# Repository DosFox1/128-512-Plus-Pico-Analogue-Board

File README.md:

**A Pico ATX and Pi Pico Power Supply and Scan Converter for the Macintosh 128/512/Plus**

A board to power a Macintosh 128/512/Plus from a Pico ATX PSU, as well as to generate a VGA video signal from an onboard Pico scan converter.
This board was designed inconjunction with the Sony SND Replacement to support my work on the Macintosh Plus clone.

**So, What Is It?**

This is a combined power supply and VGA scan converter for a Macintosh 128/512 or Plus.
The VGA scan converter is based off the work by the GuruThree:
https://github.com/guruthree/mac-se-video-converter

The firmware for the Pico is available within that repository.
The hardware for the VGA scan converter is based off of the VGA reference design as provided here:
https://datasheets.raspberrypi.com/rp2040/hardware-design-with-rp2040.pdf

The PSU portion of the deisgn is intended to be used with a Pico PSU, although any suitable ATX PSU can be used. 
The connector is identical to that of the Macintosh 128/512/Plus, so either a Molex KK396 11 way connector can be installed with an appropriate cable,
or the board can be soldered directly to the Macintosh Logic Board.
 
VDEV1 units have been assembled and worked first time. No modifications to the board were necessary at all. Additionally, I have built an equivalent system using a Pimoroni VGA board (as per the original repository) and with a Pico ATX PSU.

**Additional Features**

Aside from providing Power and a VGA signal from the Logic board, it also has some additional features:

1) Option for Composite Video with associated jumper -  the scan converter can be compiled to generate a PAL video signal from the red channel,
as such, there is an RCA connector with a jumper to select whether the required output.
Please note that the firmware will need to be recompiled with the PAL video option, and the video signal is known to be quite poor.
It's something to be fixed at some point.

2) Pads for -5v and -12V, as well as a -5v regulator - the regulator and pads are provided in case the user is intending to use the Sony SND replacement
(https://github.com/DosFox1/Sony-SND-THT-Replacement/tree/main), or if a board is installed that requires off board -5v to be regulated (such as an SE)
In normal operation, the -5v regulator and pads are not needed, and can be DNF'd (Do Not Fit).

3) Optional potential divider - the original scan converter does call for the use of a standard voltage level shifter, it was found that the 128/512/Plus appear to output
a signal that was lower than what the level shifter expected, resulting in the system not working. Further investigation reveals that the output from the board is in the region
of 3.8v - which is in the limits of a V1 Pico, as well as V2 Pico (which are 5v tolerant). Regardless, current limiting resistors have been added, and if so desired, additional resistors can be added (or diodes!) for added protection. This is a VDEV1 design, so extra protection may be added for the next iteration. Your mileage may vary!

5) Speaker pin header - the speaker output is routed to a separate pin header, to make it easier to add an external speaker.

6) RTC diodes and battery option - two diodes have been added, as well as an additional header to add a 4.5v battery pack for the RTC.
I would suggest ensuring that the battery pack is stored well away from the logic board and the analogue board, to avoid battery leakage.

7) Power Supply Switch with pads - external power switch with pads has been added, allowing the user to install either a switch at the rear of the unit, or to add an external toggle switch to power the system on, if so desired.

8) Onboard Power LED and external pads - onboard power LED is provided to prove that the 5v rail has powered up. Also the option to mount an LED elsewhere within the case if so desired.

**Part List**

Much like the Sony SND, the parts are relatively easy to source, although there may be some difficulty finding the precision value resistors. 
The parts are as follows:

<pre>
Part     Value            Device                       Package                 Library             Sheet

C1       100n 50V         100N_TH_CAP                  CAP_5.08MM_PITCH        Capacitors TH       1
C2       100n 50V         100N_TH_CAP                  CAP_5.08MM_PITCH        Capacitors TH       1
CN1      V06-1x20-SV-GF-1 PICO_BOARD                   PICO_SOCKET             uProcessor          1
CN2      2way             PIN_HEADER_2W_VERT_TH        2W_2.54MM_PITCH_VERT_TH Connectors          1
CN3      2way             PIN_HEADER_2W_VERT_TH        2W_2.54MM_PITCH_VERT_TH Connectors          1
CN4      V06-1x3-SV-GF-1  PIN_HEADER_3W_VERT_FEMALE_TH 3W_2.54MM_PITCH_VERT_TH Connectors          1
CN5      2way             PIN_HEADER_2W_VERT_TH        2W_2.54MM_PITCH_VERT_TH Connectors          1
CN6      2way             PIN_HEADER_2W_VERT_TH        2W_2.54MM_PITCH_VERT_TH Connectors          1
CN7      DB15             DB15                         DB15                    SparkFun-Retired    1
CN8      ATX24RH          ATX24RH                      ATX24_RIGHT_ANGLE       SparkFun-Connectors 1
CN9      RCA              RCA                          RCA                     SparkFun-Connectors 1
CN10     11 Way KK        KK-156-11                    KK-156-11               con-molex           1
D1       1N4004           1N4004                       DO41-10                 adafruit            1
D2       1N4004           1N4004                       DO41-10                 adafruit            1
LED1     Red              5MM_LED_RED                  5MM_TH_VERT_STANDARD    Optoelectronics     1
R1       470R             470R_TH_RESISTOR             RESISTORTHRUHOLE        Resistors TH        1
R2       47R              47R_TH_RESISTOR              RESISTORTHRUHOLE        Resistors TH        1
R3       47R              47R_TH_RESISTOR              RESISTORTHRUHOLE        Resistors TH        1
R4       1k               1K_TH_RESISTOR               RESISTORTHRUHOLE        Resistors TH        1
R5       2k               2K_TH_RESISTOR               RESISTORTHRUHOLE        Resistors TH        1
R6       4k02             4K02_TH_RESISTOR             RESISTORTHRUHOLE        Resistors TH        1
R7       8k06             8K06_TH_RESISTOR             RESISTORTHRUHOLE        Resistors TH        1
R8       499R             499R_TH_RESISTOR             RESISTORTHRUHOLE        Resistors TH        1
R9       1k               1K_TH_RESISTOR               RESISTORTHRUHOLE        Resistors TH        1
R10      2k               2K_TH_RESISTOR               RESISTORTHRUHOLE        Resistors TH        1
R11      4k02             4K02_TH_RESISTOR             RESISTORTHRUHOLE        Resistors TH        1
R12      8k06             8K06_TH_RESISTOR             RESISTORTHRUHOLE        Resistors TH        1
R13      499R             499R_TH_RESISTOR             RESISTORTHRUHOLE        Resistors TH        1
R14      1k               1K_TH_RESISTOR               RESISTORTHRUHOLE        Resistors TH        1
R15      2k               2K_TH_RESISTOR               RESISTORTHRUHOLE        Resistors TH        1
R16      4k02             4K02_TH_RESISTOR             RESISTORTHRUHOLE        Resistors TH        1
R17      8k06             8K06_TH_RESISTOR             RESISTORTHRUHOLE        Resistors TH        1
R18      499R             499R_TH_RESISTOR             RESISTORTHRUHOLE        Resistors TH        1
R19      22R              22R_TH_RESISTOR              RESISTORTHRUHOLE        Resistors TH        1
R20      22R              22R_TH_RESISTOR              RESISTORTHRUHOLE        Resistors TH        1
R21      22R              22R_TH_RESISTOR              RESISTORTHRUHOLE        Resistors TH        1
R22      DNF              22R_TH_RESISTOR              RESISTORTHRUHOLE        Resistors TH        1
R23      DNF              22R_TH_RESISTOR              RESISTORTHRUHOLE        Resistors TH        1
R24      DNF              22R_TH_RESISTOR              RESISTORTHRUHOLE        Resistors TH        1
SP1      1PIN             1PIN                         1PIN                    generic parts       1
SP2      1PIN             1PIN                         1PIN                    generic parts       1
SW1      SS12D16-GDN5     SS12D16-GDN5                 THRUHOLE90DEGSLIDESW    Switches            1
VREG1                     7905T                        TO220H                  linear              1
</pre>

**Notes on Assembly**

The board has been designed so anyone with a decent amount of soldering experience should be able to assemble one. 
The PCBs themselves can be ordered from your favourite PCB fab house, mine have been ordered from JLCPCB (sorry PCBWay).
Owing to the fact that the board is a relatively simple two layer design, the boards shouldn't be too expensive.
The cost of my boards came to $2 for five, but should usually be $4 for five PCBs - regardless - they are cheap!
The firmware that generates a VGA signal and targets a standard V1 Pico (RP2040 based) has been added to this repository. 
Pico2 (RP2354) and PAL video versions will be added eventually. Current firmware now fixes an annoying issue where the video output
was distinctly yellow - this has now been fixed.
For assembling into cases, SVGs of the board have been added - just import the board edge file to your favourite SVG editor to start designing a case for it!

**Note On The License**
The hardware design is based on the CERN Open Hardware Licence Version 2 - Strongly Reciprocal, however, the software is covered by the original MIT License. Please see:
https://github.com/guruthree/mac-se-video-converter/

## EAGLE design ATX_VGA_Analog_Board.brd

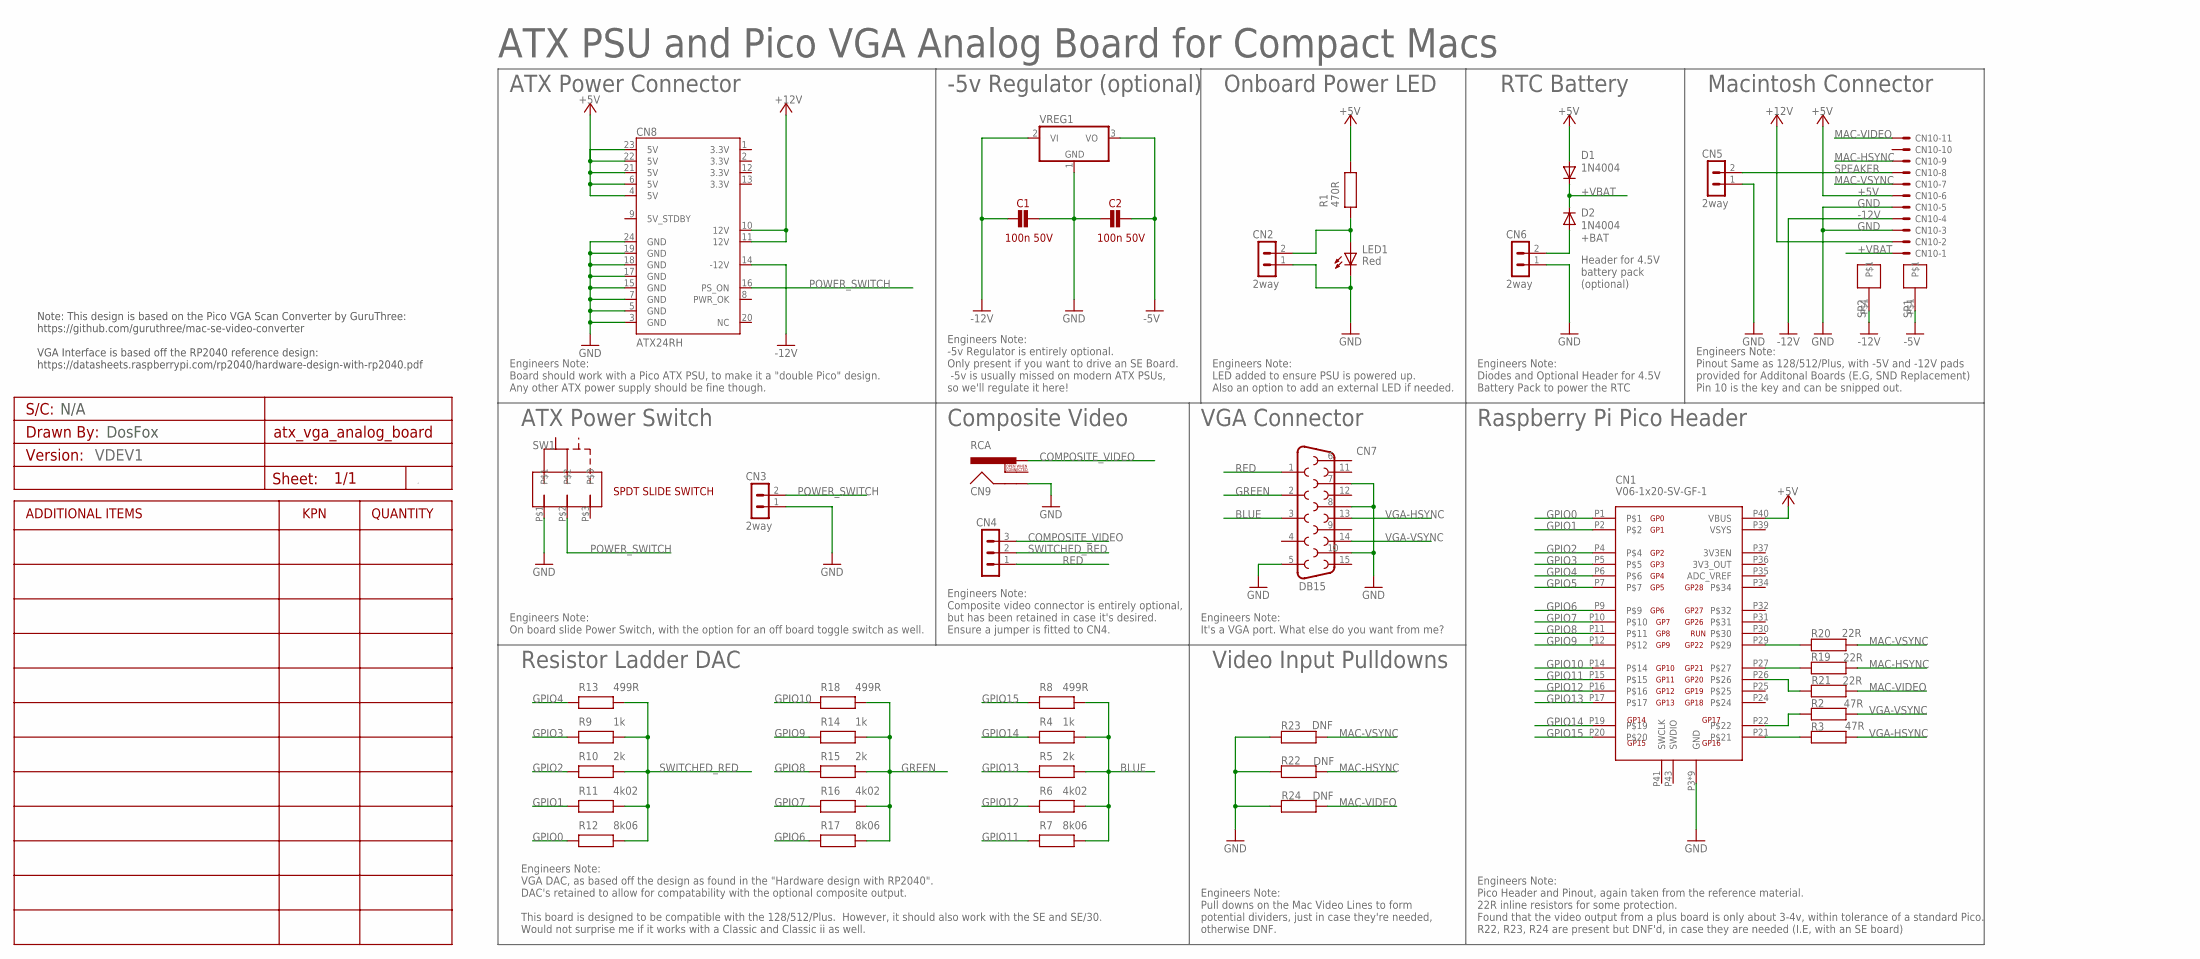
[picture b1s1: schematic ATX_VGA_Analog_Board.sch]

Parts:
A1: VDEV1; PCB_CUSTOM_DETAILS
C1, C2: 100n 50V; CAP_5.08MM_PITCH
CN1: V06-1x20-SV-GF-1; PICO_SOCKET
CN2, CN3, CN5, CN6: 2way; 2W_2.54MM_PITCH_VERT_TH
CN4: V06-1x3-SV-GF-1; 3W_2.54MM_PITCH_VERT_TH
CN7: DB15
CN8: ATX24RH; ATX24_RIGHT_ANGLE
CN9: RCA
CN10: KK-156-11
D1, D2: 1N4004; DO41-10
LED1: Red; 5MM_TH_VERT_STANDARD
R1: 470R; RESISTORTHRUHOLE
R2, R3: 47R; RESISTORTHRUHOLE
R4, R9, R14: 1k; RESISTORTHRUHOLE
R5, R10, R15: 2k; RESISTORTHRUHOLE
R6, R11, R16: 4k02; RESISTORTHRUHOLE
R7, R12, R17: 8k06; RESISTORTHRUHOLE
R8, R13, R18: 499R; RESISTORTHRUHOLE
R19, R20, R21: 22R; RESISTORTHRUHOLE
R22, R23, R24: DNF; RESISTORTHRUHOLE
SP1, SP2: 1PIN
SW1: SS12D16-GDN5; THRUHOLE90DEGSLIDESW
VREG1: 7905T; TO220H

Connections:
+5V: CN1.P40 (VBUS), CN8.4 (5V), CN8.6 (5V), CN8.21 (5V), CN8.22 (5V), CN8.23 (5V), CN10.6, D1.A, R1.P$2
+12V: CN8.10 (12V), CN8.11 (12V), CN10.2
+BAT: CN6.2, D2.A
+VBAT: CN10.1, D1.C, D2.C
-5V: C2.P$2, SP1.P$1, VREG1.3 (VO)
-12V: C1.P$1, CN8.14 (-12V), CN10.4, SP2.P$1, VREG1.2 (VI)
BLUE: CN7.3, R4.P$2, R5.P$2, R6.P$2, R7.P$2, R8.P$2
COMPOSITE_VIDEO: CN4.3, CN9.PIN
GND: C1.P$2, C2.P$1, CN1.P3 (GND), CN1.P8 (GND), CN1.P13 (GND), CN1.P18 (GND), CN1.P23 (GND), CN1.P28 (GND), CN1.P33 (GND), CN1.P38 (GND), CN1.P42 (GND), CN2.1, CN3.1, CN5.1, CN6.1, CN7.5, CN7.7, CN7.8, CN7.10, CN8.3 (GND), CN8.5 (GND), CN8.7 (GND), CN8.15 (GND), CN8.17 (GND), CN8.18 (GND), CN8.19 (GND), CN8.24 (GND), CN9.SHELL, CN10.3, CN10.5, LED1.C, R22.P$1, R23.P$1, R24.P$1, SW1.P$1, VREG1.1 (GND)
GPIO0: CN1.P1, R12.P$1
GPIO1: CN1.P2, R11.P$1
GPIO2: CN1.P4, R10.P$1
GPIO3: CN1.P5, R9.P$1
GPIO4: CN1.P6, R13.P$1
GPIO5: CN1.P7
GPIO6: CN1.P9, R17.P$1
GPIO7: CN1.P10, R16.P$1
GPIO8: CN1.P11, R15.P$1
GPIO9: CN1.P12, R14.P$1
GPIO10: CN1.P14, R18.P$1
GPIO11: CN1.P15, R7.P$1
GPIO12: CN1.P16, R6.P$1
GPIO13: CN1.P17, R5.P$1
GPIO14: CN1.P19, R4.P$1
GPIO15: CN1.P20, R8.P$1
GREEN: CN7.2, R14.P$2, R15.P$2, R16.P$2, R17.P$2, R18.P$2
MAC-HSYNC: CN10.9, R19.P$2, R22.P$2
MAC-VIDEO: CN10.11, R21.P$2, R24.P$2
MAC-VSYNC: CN10.7, R20.P$2, R23.P$2
unnamed: CN2.2, LED1.A, R1.P$1
unnamed: CN1.P22, R2.P$1
unnamed: CN1.P21, R3.P$1
unnamed: CN1.P29, R20.P$1
unnamed: CN1.P27, R19.P$1
unnamed: CN1.P26, R21.P$1
POWER_SWITCH: CN3.2, CN8.16 (PS_ON), SW1.P$2
RED: CN4.1, CN7.1
SPEAKER: CN5.2, CN10.8
SWITCHED_RED: CN4.2, R9.P$2, R10.P$2, R11.P$2, R12.P$2, R13.P$2
VGA-HSYNC: CN7.13, R3.P$2
VGA-VSYNC: CN7.14, R2.P$2

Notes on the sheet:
Note: This design is based on the Pico VGA Scan Converter by GuruThree: https://github.com/guruthree/mac-se-video-converter VGA Interface is based off the RP2040 reference design: https://datasheets.raspberrypi.com/rp2040/hardware-design-with-rp2040.pdf
DosFox
N/A
ATX PSU and Pico VGA Analog Board for Compact Macs
ATX Power Connector
Onboard Power LED
Macintosh Connector
VGA Connector
ATX Power Switch
Composite Video
-5v Regulator (optional)
Resistor Ladder DAC
RTC Battery
Raspberry Pi Pico Header
Engineers Note: Pinout Same as 128/512/Plus, with -5V and -12V pads provided for Additonal Boards (E.G, SND Replacement) Pin 10 is the key and can be snipped out.
Engineers Note: LED added to ensure PSU is powered up. Also an option to add an external LED if needed.
Header for 4.5V battery pack (optional)
Engineers Note: Diodes and Optional Header for 4.5V Battery Pack to power the RTC
Engineers Note: -5v Regulator is entirely optional. Only present if you want to drive an SE Board. -5v is usually missed on modern ATX PSUs, so we'll regulate it here!
Engineers Note: Composite video connector is entirely optional, but has been retained in case it's desired. Ensure a jumper is fitted to CN4.
Engineers Note: On board slide Power Switch, with the option for an off board toggle switch as well.
Engineers Note: VGA DAC, as based off the design as found in the "Hardware design with RP2040". DAC's retained to allow for compatability with the optional composite output. This board is designed to be compatible with the 128/512/Plus. However, it should also work with the SE and SE/30. Would not 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
Engineers Note: Pull downs on the Mac Video Lines to form potential dividers, just in case they're needed, otherwise DNF.
Engineers Note: Pico Header and Pinout, again taken from the reference material. 22R inline resistors for some protection. Found that the video output from a plus board is only about 3-4v, within tolerance of a standard Pico. R22, R23, R24 are present but DNF'd, in case they are needed (I.E, with a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
Video Input Pulldowns
Engineers Note: It's a VGA port. What else do you want from me?
Engineers Note: Board should work with a Pico ATX PSU, to make it a "double Pico" design. Any other ATX power supply should be fine though.

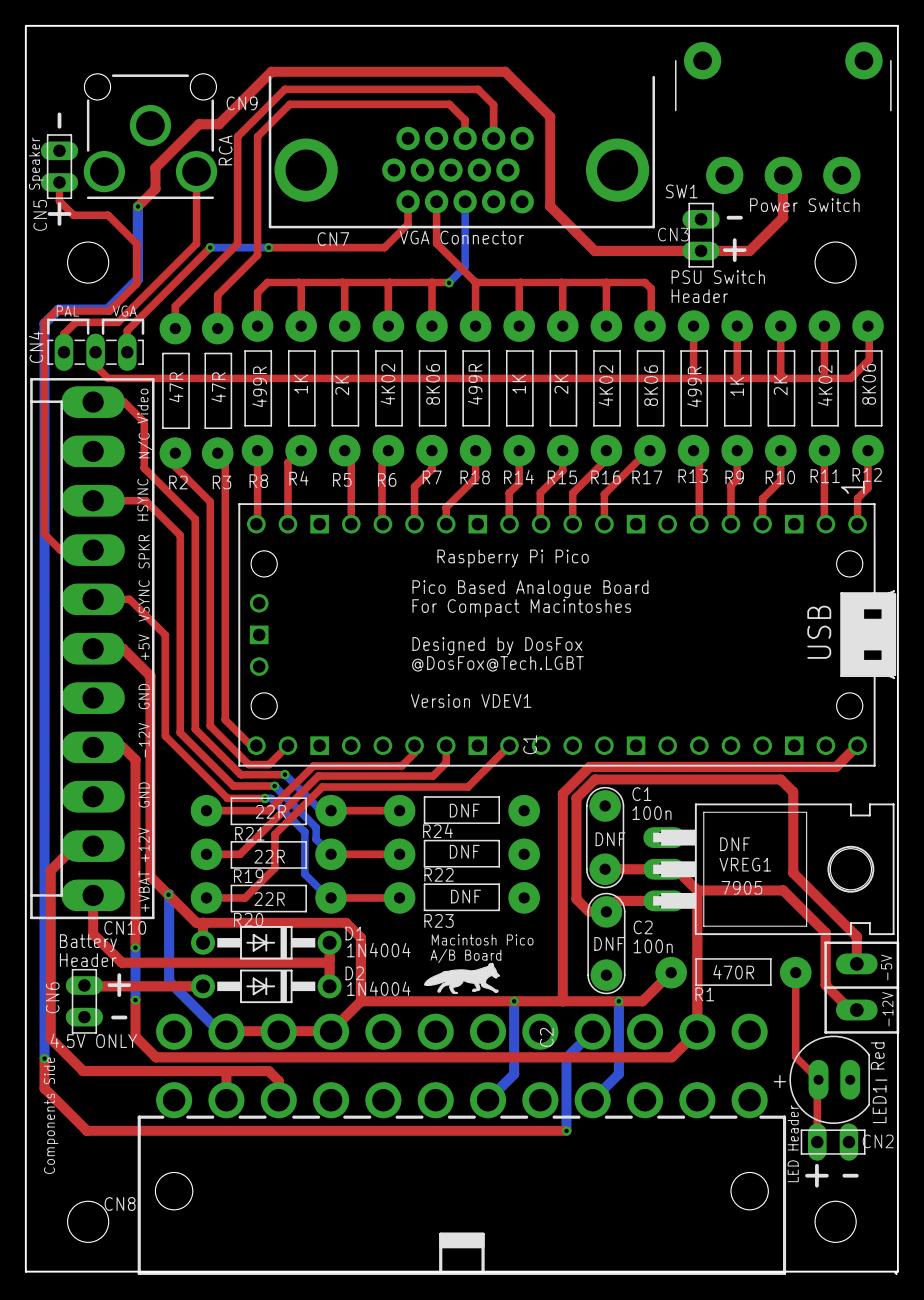
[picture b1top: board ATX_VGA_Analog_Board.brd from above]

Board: 2 copper layers, 70.0 x 100.2 mm, 44 parts (0 on the bottom side), 40 nets.

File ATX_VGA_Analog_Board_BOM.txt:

Partlist

Exported from ATX_VGA_Analog_Board.sch at 16/Aug/24 15:45

EAGLE Version 9.6.2 Copyright (c) 1988-2020 Autodesk, Inc.

Assembly variant: 

Part     Value            Device                       Package                 Library             Sheet

C1       100n 50V         100N_TH_CAP                  CAP_5.08MM_PITCH        Capacitors TH       1
C2       100n 50V         100N_TH_CAP                  CAP_5.08MM_PITCH        Capacitors TH       1
CN1      V06-1x20-SV-GF-1 PICO_BOARD                   PICO_SOCKET             uProcessor          1
CN2      2way             PIN_HEADER_2W_VERT_TH        2W_2.54MM_PITCH_VERT_TH Connectors          1
CN3      2way             PIN_HEADER_2W_VERT_TH        2W_2.54MM_PITCH_VERT_TH Connectors          1
CN4      V06-1x3-SV-GF-1  PIN_HEADER_3W_VERT_FEMALE_TH 3W_2.54MM_PITCH_VERT_TH Connectors          1
CN5      2way             PIN_HEADER_2W_VERT_TH        2W_2.54MM_PITCH_VERT_TH Connectors          1
CN6      2way             PIN_HEADER_2W_VERT_TH        2W_2.54MM_PITCH_VERT_TH Connectors          1
CN7      DB15             DB15                         DB15                    SparkFun-Retired    1
CN8      ATX24RH          ATX24RH                      ATX24_RIGHT_ANGLE       SparkFun-Connectors 1
CN9      RCA              RCA                          RCA                     SparkFun-Connectors 1
CN10                      KK-156-11                    KK-156-11               con-molex           1
D1       1N4004           1N4004                       DO41-10                 adafruit            1
D2       1N4004           1N4004                       DO41-10                 adafruit            1
LED1     Red              5MM_LED_RED                  5MM_TH_VERT_STANDARD    Optoelectronics     1
R1       470R             470R_TH_RESISTOR             RESISTORTHRUHOLE        Resistors TH        1
R2       47R              47R_TH_RESISTOR              RESISTORTHRUHOLE        Resistors TH        1
R3       47R              47R_TH_RESISTOR              RESISTORTHRUHOLE        Resistors TH        1
R4       1k               1K_TH_RESISTOR               RESISTORTHRUHOLE        Resistors TH        1
R5       2k               2K2_TH_RESISTOR              RESISTORTHRUHOLE        Resistors TH        1
R6       4k02             4K7_TH_RESISTOR              RESISTORTHRUHOLE        Resistors TH        1
R7       8k06             68K_TH_RESISTOR              RESISTORTHRUHOLE        Resistors TH        1
R8       499R             470R_TH_RESISTOR             RESISTORTHRUHOLE        Resistors TH        1
R9       1k               1K_TH_RESISTOR               RESISTORTHRUHOLE        Resistors TH        1
R10      2k               2K2_TH_RESISTOR              RESISTORTHRUHOLE        Resistors TH        1
R11      4k02             4K7_TH_RESISTOR              RESISTORTHRUHOLE        Resistors TH        1
R12      8k06             68K_TH_RESISTOR              RESISTORTHRUHOLE        Resistors TH        1
R13      499R             470R_TH_RESISTOR             RESISTORTHRUHOLE        Resistors TH        1
R14      1k               1K_TH_RESISTOR               RESISTORTHRUHOLE        Resistors TH        1
R15      2k               2K2_TH_RESISTOR              RESISTORTHRUHOLE        Resistors TH        1
R16      4k02             4K7_TH_RESISTOR              RESISTORTHRUHOLE        Resistors TH        1
R17      8k06             68K_TH_RESISTOR              RESISTORTHRUHOLE        Resistors TH        1
R18      499R             470R_TH_RESISTOR             RESISTORTHRUHOLE        Resistors TH        1
R19      22R              22R_TH_RESISTOR              RESISTORTHRUHOLE        Resistors TH        1
R20      22R              22R_TH_RESISTOR              RESISTORTHRUHOLE        Resistors TH        1
R21      22R              22R_TH_RESISTOR              RESISTORTHRUHOLE        Resistors TH        1
R22      DNF              22R_TH_RESISTOR              RESISTORTHRUHOLE        Resistors TH        1
R23      DNF              22R_TH_RESISTOR              RESISTORTHRUHOLE        Resistors TH        1
R24      DNF              22R_TH_RESISTOR              RESISTORTHRUHOLE        Resistors TH        1
SP1      1PIN             1PIN                         1PIN                    generic parts       1
SP2      1PIN             1PIN                         1PIN                    generic parts       1
SW1      SS12D16-GDN5     SS12D16-GDN5                 THRUHOLE90DEGSLIDESW    Switches            1
VREG1                     7905T                        TO220H                  linear              1

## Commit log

2024-08-21 Add files via upload
    Added corrected BOM
2024-08-21 Update README.md
    Updated BOM list
2024-10-21 Add files via upload
    As found by HKZ on Mastodon (@hkz@chinwag.org) the "WHITE" variable in the original Scan converter repo (https://github.com/guruthree/mac-se-video-converter) was defined as 0x7FFF. This resulted in a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
2024-10-21 Rename Scan Converter - PAL- corrected white.uf2 to Firmware/Scan Converter - PAL- corrected white.uf2
2024-10-21 Rename Scan Converter - VGA -corrected white.uf2 to Firmware/Scan Converter - VGA -corrected white.uf2
2024-10-21 Rename ATX_VGA_Analog_Board.brd to EAGLE/ATX_VGA_Analog_Board.brd
2024-10-21 Rename ATX_VGA_Analog_Board.sch to EAGLE/ATX_VGA_Analog_Board.sch
2024-10-21 Rename ATX_VGA_Analog_Board_Schematics.pdf to Schematics/ATX_VGA_Analog_Board_Schematics.pdf
2024-10-21 Rename ATX_VGA_Analog_Board_VDEV1_Gerbers.zip to Gerbers/ATX_VGA_Analog_Board_VDEV1_Gerbers.zip
2024-10-21 Rename ATX_VGA_Analog_Board_VDEV1_SVG_Files.zip to Images/ATX_VGA_Analog_Board_VDEV1_SVG_Files.zip
2024-10-21 Rename Pico Analogue Board Bare PCB.png to Images/Pico Analogue Board Bare PCB.png
2024-10-21 Rename PicoABBoardBack.png to Images/PicoABBoardBack.png
2024-10-21 Rename PicoABBoardFront.png to Images/PicoABBoardFront.png
2024-10-21 Add files via upload
    Can Github not accidentally delete a file for FIVE MINUTES.
2024-10-21 Create LICENSE
    Added CERN Strongly Reciprocal License - this is for the hardware only. Software is covered by the MIT License.
2024-10-21 Update LICENSE

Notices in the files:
parts and their libraries:
SparkFun-Retired: Licensing: Creative Commons ShareAlike 4.0 International - https://creativecommons.org/licenses/by-sa/4.0
